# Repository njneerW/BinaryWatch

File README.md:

# BinaryWatch
TODO:
code is complex enough that it should not be contained entirely in one file.
Seperate out by functionality.

    *display functions
    *RTCC functions
    *deep sleep functions
    *timer functions

Debounce function is actually pretty useful.  Make a library out of it.

    *See if the timers are similar enough that a timer struct can be passed
     in to make the function more generic
    *Pass in the port for the button to debounce (w/ active high v low)
    *Parameterize DEBOUNCE, and HOLD values
    *Make a pushbutton structure, obviating the need for global state vars

If we're making libraries, lets do something about RTCC.  It's begging
    for a simple API interface.

Start properly using the RTCC lock/unlock capability to protect RTCC from
    unintentional modifications.

PIC18F24J11 driven LED binary wrist watch.

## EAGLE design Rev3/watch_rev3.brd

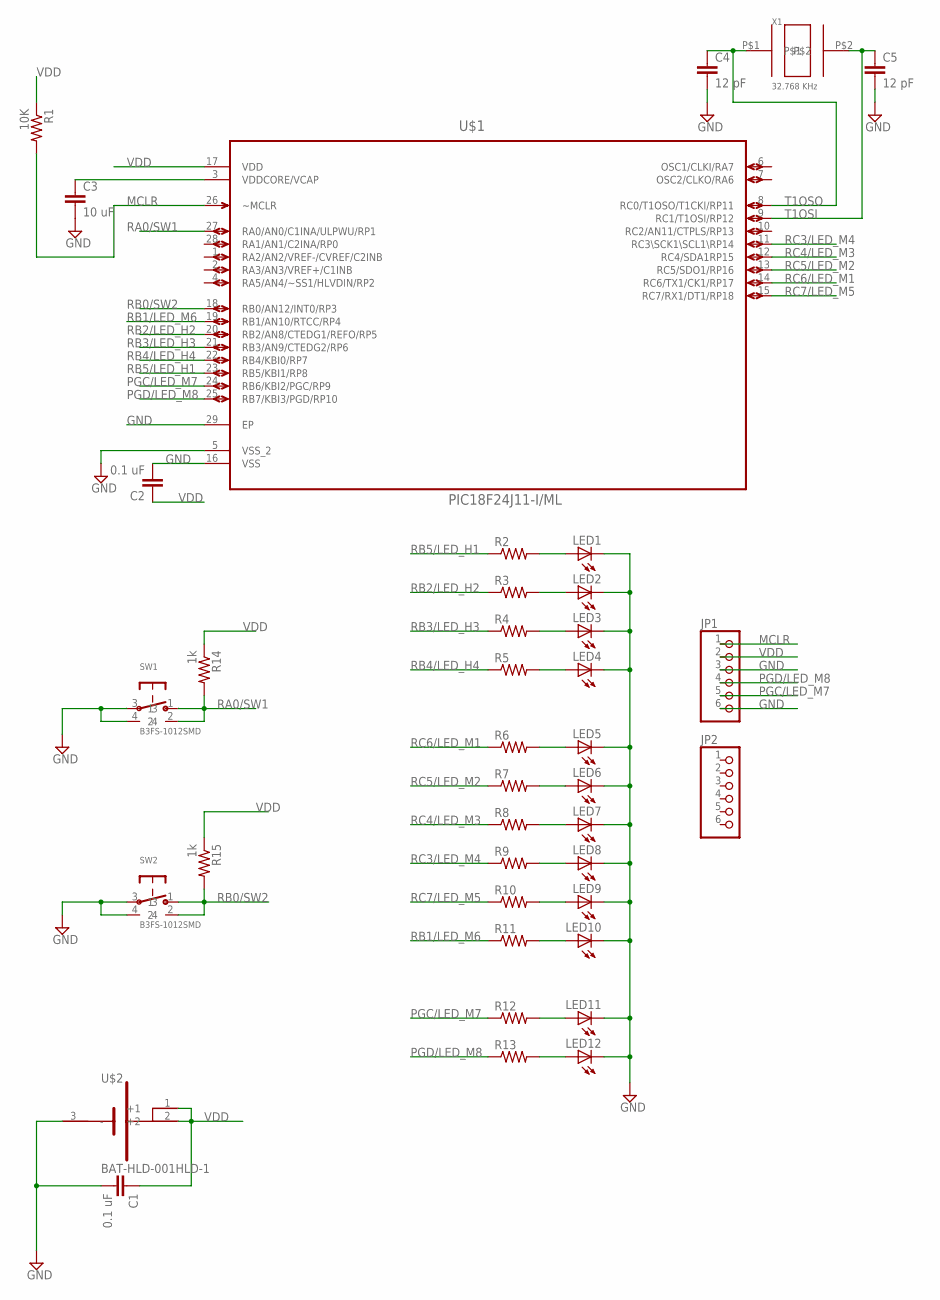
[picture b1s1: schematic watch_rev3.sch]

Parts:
C1, C2: 0.1 uF; C0603
C3: 10 uF; C0603
C4, C5: 12 pF; C0603
JP1, JP2: PINHD-1X6; 1X06
LED1, LED2, LED3, LED4, LED5, LED6, LED7, LED8, LED9, LED10, LED11, LED12: LEDCHIPLED_0603; CHIPLED_0603
R1: 10K; R0603
R2, R3, R4, R5, R6, R7, R8, R9, R10, R11, R12, R13: R-US_R0603; R0603
R14, R15: 1k; R0603
SW1, SW2: B3FS-1012SMD; B3FS-1012
U$1: PIC18F24J11-I/ML; QFN65P600X600X100-29N
U$2: BAT-HLD-001HLD-1; BAT-HLD-001
X1: 32.768 KHz; XTAL_3.2X1.5

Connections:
GND: C1.2, C2.2, C3.2, C4.2, C5.2, JP1.3, JP1.6, LED1.C, LED2.C, LED3.C, LED4.C, LED5.C, LED6.C, LED7.C, LED8.C, LED9.C, LED10.C, LED11.C, LED12.C, SW1.3, SW1.4, SW2.3, SW2.4, U$1.5 (VSS_2), U$1.16 (VSS), U$1.29 (EP), U$2.3 (-)
MCLR: JP1.1, R1.2, U$1.26 (~MCLR)
unnamed: LED1.A, R2.2
unnamed: LED2.A, R3.2
unnamed: C3.1, U$1.3 (VDDCORE/VCAP)
unnamed: LED3.A, R4.2
unnamed: LED4.A, R5.2
unnamed: LED5.A, R6.2
unnamed: LED6.A, R7.2
unnamed: LED7.A, R8.2
unnamed: LED8.A, R9.2
unnamed: LED9.A, R10.2
unnamed: LED10.A, R11.2
unnamed: LED11.A, R12.2
unnamed: LED12.A, R13.2
PGC/LED_M7: JP1.5, R12.1, U$1.24 (RB6/KBI2/PGC/RP9)
PGD/LED_M8: JP1.4, R13.1, U$1.25 (RB7/KBI3/PGD/RP10)
RA0/SW1: R14.2, SW1.1, SW1.2, U$1.27 (RA0/AN0/C1INA/ULPWU/RP1)
RB0/SW2: R15.2, SW2.1, SW2.2, U$1.18 (RB0/AN12/INT0/RP3)
RB1/LED_M6: R11.1, U$1.19 (RB1/AN10/RTCC/RP4)
RB2/LED_H2: R3.1, U$1.20 (RB2/AN8/CTEDG1/REFO/RP5)
RB3/LED_H3: R4.1, U$1.21 (RB3/AN9/CTEDG2/RP6)
RB4/LED_H4: R5.1, U$1.22 (RB4/KBI0/RP7)
RB5/LED_H1: R2.1, U$1.23 (RB5/KBI1/RP8)
RC3/LED_M4: R9.1, U$1.11 (RC3\SCK1\SCL1\RP14)
RC4/LED_M3: R8.1, U$1.12 (RC4/SDA1RP15)
RC5/LED_M2: R7.1, U$1.13 (RC5/SDO1/RP16)
RC6/LED_M1: R6.1, U$1.14 (RC6/TX1/CK1/RP17)
RC7/LED_M5: R10.1, U$1.15 (RC7/RX1/DT1/RP18)
T1OSI: C5.1, U$1.9 (RC1/T1OSI/RP12), X1.P$2
T1OSO: C4.1, U$1.8 (RC0/T1OSO/T1CKI/RP11), X1.P$1
VDD: C1.1, C2.1, JP1.2, R1.1, R14.1, R15.1, U$1.17 (VDD), U$2.1 (+1), U$2.2 (+2)

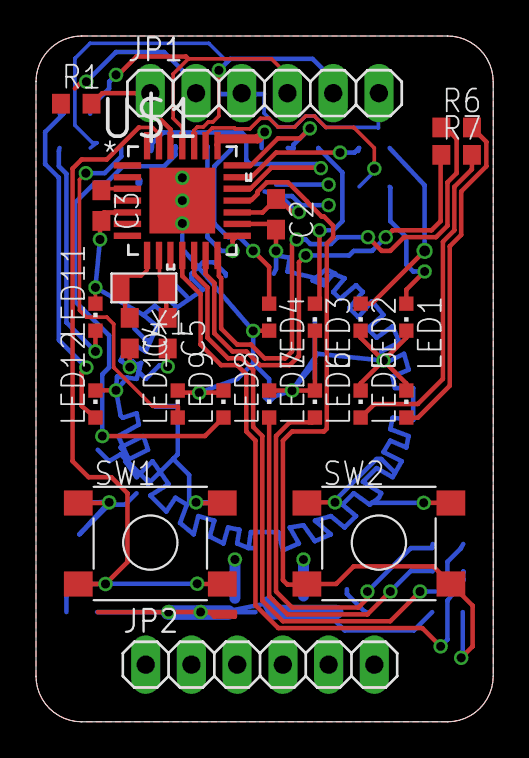
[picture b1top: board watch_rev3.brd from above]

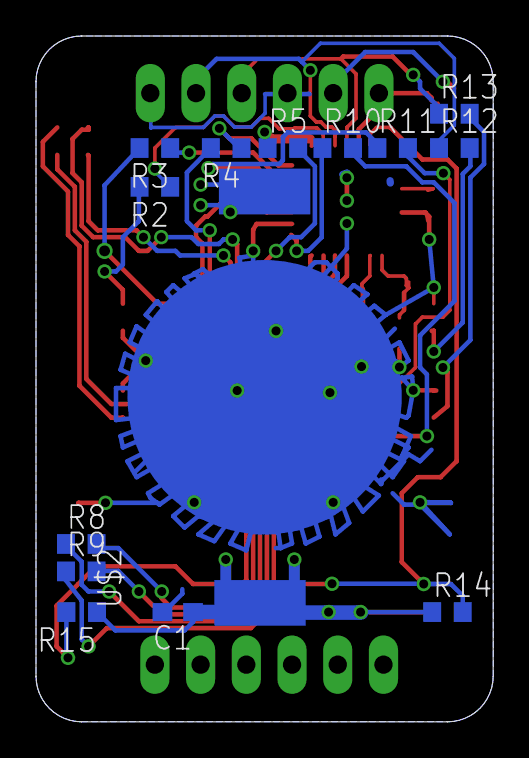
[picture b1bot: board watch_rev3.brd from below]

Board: 2 copper layers, 25.4 x 38.1 mm, 39 parts (14 on the bottom side), 32 nets.

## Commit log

2015-03-02 Added initial files to github
2015-03-03 Updated all LED port/pin references to instead use macros. I don't foresee the pinout changing at this point, but that will make it much easier to modify update and read functions if LED port/pins ev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
2015-03-19 Added todo list to README, in case I ever get bored
2015-03-19 Syntax test
2015-03-19 more syntax
2015-03-19 ...I should really figure out how .md files work
